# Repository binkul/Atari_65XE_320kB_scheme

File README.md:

# Atari_65XE_320kB_scheme

It is working, but there is problem with video. The image on the monitor is not clear. There is a lot of white vertical stripes - probably wrong GND project. 
There can be used up to four diffrent OS and eight internal languages, like MAC65, Action!, Basic XE, XL. On Board GTIA fixer and 256kB extra RAM.

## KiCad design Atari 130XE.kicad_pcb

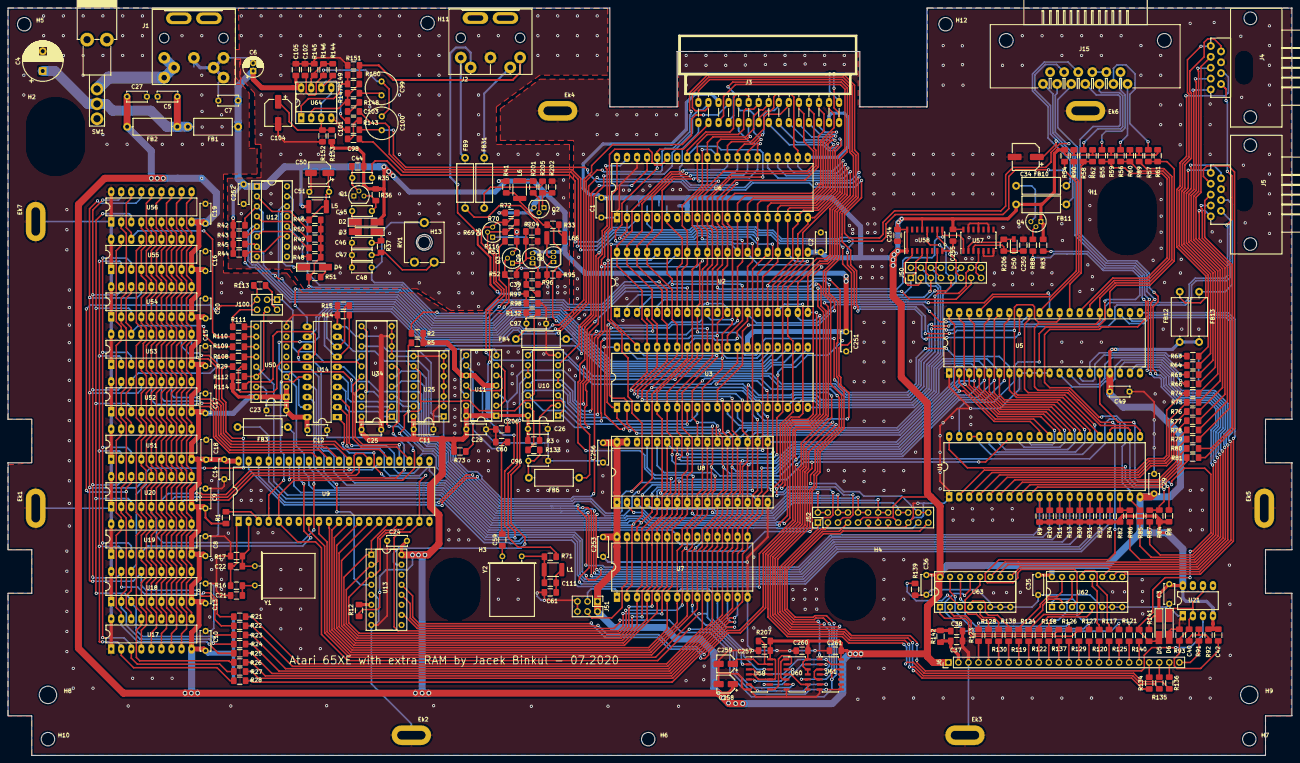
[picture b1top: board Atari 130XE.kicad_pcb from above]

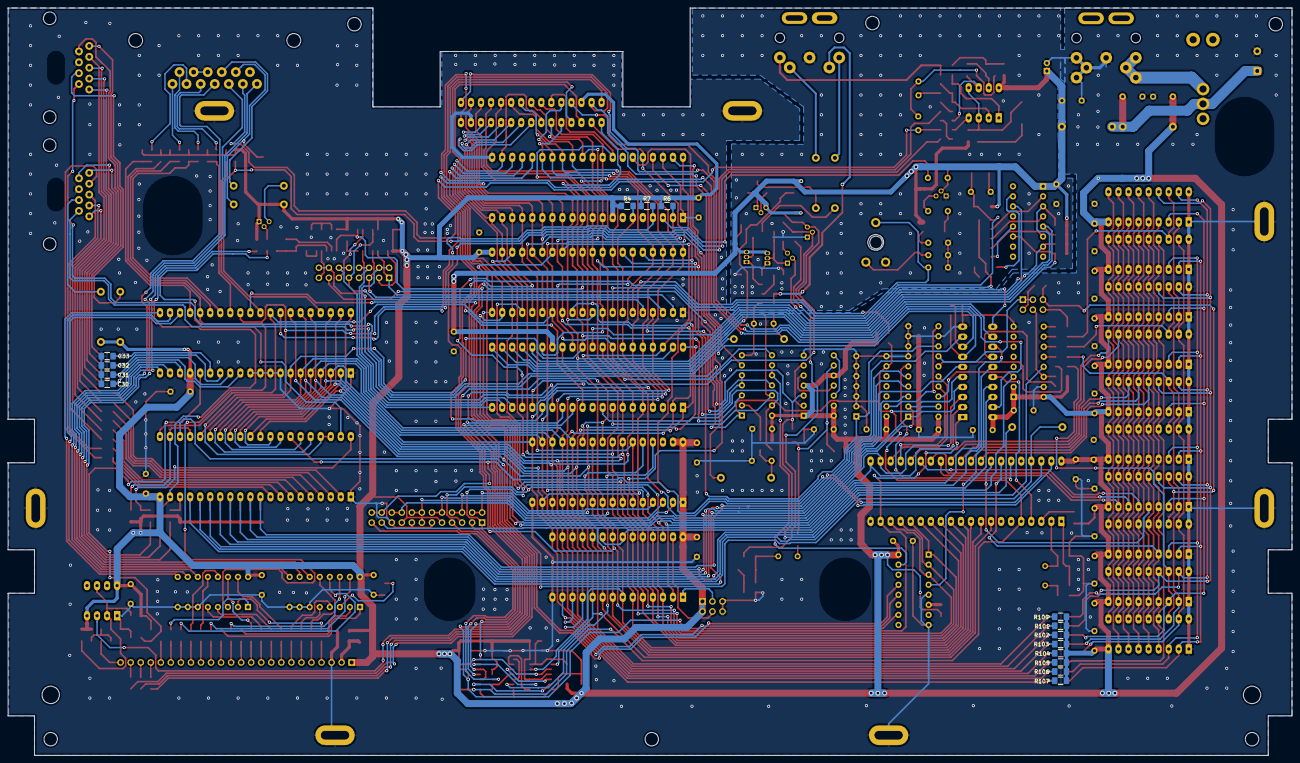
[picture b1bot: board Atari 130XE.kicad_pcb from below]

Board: 2 copper layers, 324.7 x 189.0 mm, 321 parts (15 on the bottom side), 305 nets.

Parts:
C1, C2, C3, C5, C7, C8, C15, C16, C17, C18, C19, C20, C23, C24, C25, C26, C27, C28, C29, C35, C36, C48, C49, C51, C251, C252, C253: 100nF; C_Disc_D5.0mm_W2.5mm_P5.00mm
C4: 470uF; CP_Radial_D10.0mm_P5.00mm
C6: 22uF; CP_Radial_D5.0mm_P2.00mm
C9, C10, C11, C12, C13, C14: C; C_Disc_D5.0mm_W2.5mm_P5.00mm
C21, C22: 27pF; C_1206_3216Metric_Pad1.42x1.75mm_HandSolder
C30, C31, C32, C33, C98, C103: 47nF; C_1206_3216Metric_Pad1.42x1.75mm_HandSolder
C34: 22uF; CP_Elec_6.3x5.3
C37: 10nF; C_1206_3216Metric_Pad1.42x1.75mm_HandSolder
C38, C61, C105, C254, C255, C257, C260, C261: 100nF; C_1206_3216Metric_Pad1.42x1.75mm_HandSolder
C39, C101, C102: 1nF; C_1206_3216Metric_Pad1.42x1.75mm_HandSolder
C40, C42: 100n; C_1206_3216Metric_Pad1.42x1.75mm_HandSolder
C44: 68pF; C_Disc_D5.0mm_W2.5mm_P5.00mm
C45: 220pF; C_Disc_D5.0mm_W2.5mm_P5.00mm
C46, C47, C96, C97: 1nF; C_Disc_D5.0mm_W2.5mm_P5.00mm
C50: 10uF; CP_Elec_5x5.7
C59, C206, C250: 22pF; C_1206_3216Metric_Pad1.42x1.75mm_HandSolder
C60: 560pF; C_1206_3216Metric_Pad1.42x1.75mm_HandSolder
C99, C100: 4,7uF; C_Radial_D8.0mm_H7.0mm_P3.50mm
C104: 10uF; CP_Elec_6.3x5.3
C111: 820pF; C_1206_3216Metric_Pad1.42x1.75mm_HandSolder
C256: 100nF; C_Disc_D6.0mm_W2.5mm_P5.00mm
C258: 22uF/16V; CP_Elec_4x5.3
C259: 4,7uF/35; CP_Elec_4x5.3
D2, D3, D4, D5: 1N4148; D_MiniMELF_Handsoldering
D6: 1N4001; D_MiniMELF_Handsoldering
D50: BAS316; D_SOD-323_HandSoldering
Ek1, Ek2, Ek3, Ek4, Ek5, Ek6, Ek7: Ekran_hole; Ekran_GND
FB1, FB2, FB3, FB4, FB5, FB9, FB10, FB11, FB12, FB13, FB31: Ferrite_Bead; L_Axial_L9.5mm_D4.0mm_P12.70mm_Horizontal_Fastron_SMCC
H1, H2: MountingHole; Big_hole
H3, H4: MountingHole; Medium_hole
H5, H6, H7, H10, H11, H12: MountingHole; Hole_3.4mm
H8, H9: MountingHole; Hole_4.4mm
H13: Pot hole; MountingHole_3.2mm_M3
J1: Power; DIN_7_pin
J2: DIN-5_180degree; DIN_5_pin
J3: Cartridge; Cartridge_Slot
J4, J5: Joystick_Port; Joystick_Pport
J6: Keyboard; PinHeader_1x24_P2.54mm_Vertical
J15: SIO_Port; SIO_Slot
J50: GTIA Fix; PinHeader_2x08_P2.54mm_Vertical
J51: OS Type; PinHeader_2x03_P2.54mm_Vertical
J52: Basic; PinHeader_2x12_P2.54mm_Vertical
J100: Ext_Memory_Conn; PinHeader_2x03_P2.54mm_Vertical
L1: 1,5uH; L_1812_4532Metric_Pad1.30x3.40mm_HandSolder
L5: 820uH; R_1812_4532Metric_Pad1.30x3.40mm_HandSolder
L6, L66: 100uH; L_1812_4532Metric_Pad1.30x3.40mm_HandSolder
Q1, Q2, Q3, Q6: 2N3904; TO-92
Q4: 2N3906; TO-92
Q8, Q9: PN2222A; TO-92_Inline
R1, R2, R3, R4, R5, R6, R7, R8, R9, R10, R11, R12, R13, R30, R31, R32, R34, R90, R114: 3k; R_1206_3216Metric_Pad1.42x1.75mm_HandSolder
R14, R15, R37, R41, R42, R43, R44, R45, R54, R72, R142, R146, R151, R206, R207: 1k; R_1206_3216Metric_Pad1.42x1.75mm_HandSolder
R16: 240; R_1206_3216Metric_Pad1.42x1.75mm_HandSolder
R17: 1M; R_1206_3216Metric_Pad1.42x1.75mm_HandSolder
R21, R22, R23, R24, R25, R26, R27, R28, R29, R96, R108, R109, R110, R111, R113: 33; R_1206_3216Metric_Pad1.42x1.75mm_HandSolder
R33: 5k6; R_1206_3216Metric_Pad1.42x1.75mm_HandSolder
R35: 33k; R_1206_3216Metric_Pad1.42x1.75mm_HandSolder
R36: 680; R_1206_3216Metric_Pad1.42x1.75mm_HandSolder
R46: 1k6; R_1206_3216Metric_Pad1.42x1.75mm_HandSolder
R47: 36k; R_1206_3216Metric_Pad1.42x1.75mm_HandSolder
R48: 18k; R_1206_3216Metric_Pad1.42x1.75mm_HandSolder
R49: 9k1; R_1206_3216Metric_Pad1.42x1.75mm_HandSolder
R50, R59, R60, R61, R62, R73, R82, R83, R84: 4k7; R_1206_3216Metric_Pad1.42x1.75mm_HandSolder
R51: 750; R_1206_3216Metric_Pad1.42x1.75mm_HandSolder
R52, R147: 2k; R_1206_3216Metric_Pad1.42x1.75mm_HandSolder
R53, R55, R56, R57, R58, R85, R86, R87, R91, R139: 100; R_1206_3216Metric_Pad1.42x1.75mm_HandSolder
R63, R64, R65, R66: 1k8; R_1206_3216Metric_Pad1.42x1.75mm_HandSolder
R69, R201: 6k8; R_1206_3216Metric_Pad1.42x1.75mm_HandSolder
R70, R100, R101, R102, R103, R104, R105, R106, R107, R112: 10k; R_1206_3216Metric_Pad1.42x1.75mm_HandSolder
R71, R134, R135, R136: 470; R_1206_3216Metric_Pad1.42x1.75mm_HandSolder
R74, R75, R76, R77, R78, R79, R80, R81: 120; R_1206_3216Metric_Pad1.42x1.75mm_HandSolder
R88: 2k7; R_1206_3216Metric_Pad1.42x1.75mm_HandSolder
R89, R141: 47k; R_1206_3216Metric_Pad1.42x1.75mm_HandSolder
R92, R143: 56k; R_1206_3216Metric_Pad1.42x1.75mm_HandSolder
R93, R148: 470k; R_1206_3216Metric_Pad1.42x1.75mm_HandSolder
R95, R202: 180; R_1206_3216Metric_Pad1.42x1.75mm_HandSolder
R97: 18; R_1206_3216Metric_Pad1.42x1.75mm_HandSolder
R98: 82; R_1206_3216Metric_Pad1.42x1.75mm_HandSolder
R116: 51; R_1206_3216Metric_Pad1.42x1.75mm_HandSolder
R117, R118, R119, R120, R121, R122, R123, R124, R125, R126, R127, R128, R129, R130, R132, R133, R137, R138: 220; R_1206_3216Metric_Pad1.42x1.75mm_HandSolder
R140: 270; R_1206_3216Metric_Pad1.42x1.75mm_HandSolder
R144, R152: 2k2; R_1206_3216Metric_Pad1.42x1.75mm_HandSolder
R145: 6k2; R_1206_3216Metric_Pad1.42x1.75mm_HandSolder
R149: 68k; R_1206_3216Metric_Pad1.42x1.75mm_HandSolder
R150: 5k1; R_1206_3216Metric_Pad1.42x1.75mm_HandSolder
R153: 3k3; R_1206_3216Metric_Pad1.42x1.75mm_HandSolder
R204: 47; R_1206_3216Metric_Pad1.42x1.75mm_HandSolder
R205: 150; R_1206_3216Metric_Pad1.42x1.75mm_HandSolder
RV1: R_POT; Potentiometer_ACP_CA9-V10_Vertical_Hole
SW1: Switch_power_on; Switch_ON-OFF
U1: PIA; DIP-40_W15.24mm_LongPads
U2: Antic; DIP-40_W15.24mm_LongPads
U3: GTIA; DIP-40_W15.24mm_LongPads
U5: POKEY; DIP-40_W15.24mm_LongPads
U6: Sally; DIP-40_W15.24mm_LongPads
U7: 27C512; DIP-28_W15.24mm_LongPads
U8: 27C010; DIP-32_W15.24mm_Socket_LongPads
U9: Freddie; DIP-40_W15.24mm_LongPads
U10: 74LS08; DIP-14_W7.62mm_Socket
U11: 74LS74; DIP-14_W7.62mm_Socket
U12: 4050; DIP-16_W7.62mm_Socket
U13: 74LS138; DIP-16_W7.62mm_Socket
U14: MMU; DIP-20_W7.62mm_LongPads
U17, U18, U19, U20, U51, U52, U53, U54, U55, U56: DRAM_4464; DIP-18_W7.62mm_LongPads
U21: NE555; DIP-8_W7.62mm_LongPads
U25: 74LS95; DIP-14_W7.62mm_Socket
U34: MMMU_GAL; DIP-20_W7.62mm_Socket
U50: 74LS155; DIP-16_W7.62mm_Socket
U57: 74HC14; SOIC-14_3.9x8.7mm_P1.27mm
U58: 74LS175; SOIC-16_3.9x9.9mm_P1.27mm
U59: 74HC74; SOIC-14_3.9x8.7mm_P1.27mm
U60, U61: 74HC02; SOIC-14_3.9x8.7mm_P1.27mm
U62, U63: 4051; DIP-16_W7.62mm_Socket
U64: LM358; DIP-8_W7.62mm_Socket_LongPads
Y1: 14,18757MHz; Crystal_HC18-U_Horizontal
Y2: 4.43MHz; Crystal_HC18-U_Horizontal

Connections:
+5VA: C6.1, C7.1, C105.2, C251.1, C252.1, D2.2, FB1.1, L5.1, Q2.3, Q8.3, Q9.3, R35.1, R36.1, R41.1, R42.1, R43.1, R44.1, R45.1, R72.2, R153.2, U3.27, U12.1, U64.8
A0: J3.5, U1.35, U2.13, U3.2, U5.36, U6.9, U7.10, U8.12, U9.8, U59.2
A1: J3.4, U1.36, U2.12, U3.1, U5.35, U6.10, U7.9, U8.11, U9.9
A2: J3.3, U2.11, U3.40, U5.34, U6.11, U7.8, U8.10, U9.10
A3: J3.2, U2.10, U3.39, U5.33, U6.12, U7.7, U8.9, U9.11, U59.12
A4: J3.C, U2.28, U3.38, U6.13, U7.6, U8.8, U9.12
A5: J3.D, U2.27, U6.14, U7.5, U8.7, U9.13
A6: J3.E, U2.26, U6.15, U7.4, U8.6, U9.14
A7: J3.F, U2.25, U6.16, U7.3, U8.5, U9.15
A8: J3.H, U2.24, U6.17, U7.25, U8.27, U9.16, U13.1
A9: J3.J, U2.23, U6.18, U7.24, U8.26, U9.17, U13.2
A10: J3.P, U2.16, U6.19, U7.21, U8.23, U9.18, U13.3
A11: J3.N, U2.22, U6.20, U7.23, U8.25, U9.19, U14.1
A12: J3.K, J52.1, U2.17, U6.22, U7.2, U9.21, U14.2, U61.3, U61.5
A12_cart: J52.3, U61.1
A12_sel: J52.2, J52.4, U8.4
A13: J52.5, U2.18, U6.23, U7.26, U9.22, U14.3
A13_cart: J52.7, U61.4
A13_sel: J52.6, J52.8, U8.28
A14: U2.19, U6.24, U14.4, U34.1
A14_sel: J52.10, J52.12, U8.29
A15: U2.20, U6.25, U14.5, U34.2
A15_sel: J52.14, J52.16, U8.3
A16_sel: J52.18, J52.20, U8.2
AN0: J50.1, U2.2, U58.4
AN0_FIX: J50.3, U58.2
AN1: J50.5, U2.3, U58.5
AN1_FIX: J50.7, U58.7
AN2: J50.9, U2.5, U58.12
AN2_FIX: J50.11, U58.10
AUDIO: J2.3, R150.1, R151.2
BACK0: J4.2, R75.1
BACK1: J5.2, R79.1
BASC_cart: J52.23, U60.10
BASIC: J52.21, U14.13, U60.6
BASIC_sel: J52.22, J52.24, U8.22, U8.24
BELL: C103.1, U3.15
BO2: J3.S, U1.25, U2.29, U3.30, U5.7, U10.3
BSC: J6.20, R140.1
CAS: U9.35, U34.6
CASBNK: J100.1, J100.3, U34.14
CASBNK_128: J100.5, R113.2, U19.16, U20.16
CASEXT_1: J100.6, R111.1
CASEXT_2: R108.1, U51.16, U52.16
CASEXT_3: R109.1, U53.16, U54.16
CASEXT_4: R110.1, U55.16, U56.16
CASINH: U9.4, U14.16
CASMAN: R29.2, U34.15
CCTL: J3.15, U13.10, U61.12
CHROMA: FB31.1, J2.5
CLKIN: J15.1, R56.1
CLKOUT: J15.2, R55.1
COMMAND: J15.7, R85.2
COMPOSITE: J2.4, R97.1, R98.1
D0: J3.10, R28.2, R107.2, U1.33, U2.30, U3.7, U5.38, U6.33, U7.11, U8.13
D1: J3.9, R27.2, R106.2, U1.32, U2.31, U3.6, U5.39, U6.32, U7.12, U8.14
D2: J3.8, R26.2, R105.2, U1.31, U2.32, U3.5, U5.40, U6.31, U7.13, U8.15
D3: J3.L, R25.2, R104.2, U1.30, U2.33, U3.4, U5.2, U6.30, U7.15, U8.17
D4: J3.6, R24.2, R103.2, U1.29, U2.40, U3.37, U5.3, U6.29, U7.16, U8.18
D5: J3.7, R23.2, R102.2, U1.28, U2.39, U3.36, U5.4, U6.28, U7.17, U8.19
D6: J3.11, R22.2, R101.2, U1.27, U2.38, U3.35, U5.5, U6.27, U7.18, U8.20
D7: J3.M, R21.2, R100.2, U1.26, U2.37, U3.34, U5.6, U6.26, U7.19, U8.21
DATAIN: J15.3, R57.1
DATAOUT: J15.5, R58.1
DQ0: R28.1, U17.2, U19.2, U51.2, U53.2, U55.2
DQ1: R27.1, U17.3, U19.3, U51.3, U53.3, U55.3
DQ2: R26.1, U17.15, U19.15, U51.15, U53.15, U55.15
DQ3: R25.1, U17.17, U19.17, U51.17, U53.17, U55.17
DQ4: R24.1, U18.2, U20.2, U52.2, U54.2, U56.2
DQ5: R23.1, U18.3, U20.3, U52.3, U54.3, U56.3
DQ6: R22.1, U18.15, U20.15, U52.15, U54.15, U56.15
DQ7: R21.1, U18.17, U20.17, U52.17, U54.17, U56.17
EXTSEL: R1.1, U9.3
FA14: U9.23, U34.16
FA15: U9.24, U34.17
FO0: U2.35, U3.29
FWD0: J4.1, R74.1
FWD1: J5.1, R78.1
GND: C1.2, C2.2, C3.2, C4.2, C5.2, C6.2, C7.2, C8.2, C9.2, C10.2, C11.2, C12.2, C13.2, C14.2, C15.2, C16.2, C17.2, C18.2, C19.2, C20.2, C21.2, C22.2, C23.2, C24.2, C25.2, C26.2, C27.2, C28.2, C29.2, C30.2, C31.2, C32.2, C33.2, C34.2, C35.2, C36.2, C37.2, C38.2, C46.1, C47.1, C48.1, C49.2, C50.2, C51.1, C60.2, C61.2, C96.2, C97.2, C101.1, C102.1, C104.2, C105.1, C206.2, C250.1, C251.2, C252.2, C253.2, C254.2, C255.2, C256.2, C257.2, C258.2, C259.2, C260.2, C261.2, D6.2, Ek1.1, Ek2.1, Ek3.1, Ek4.1, Ek5.1, Ek6.1, Ek7.1, J1.2, J1.3, J1.5, J1.7, J2.2, J3.B, J4.8, J5.8, J6.3, J15.4, J15.6, J51.5, J51.6, J52.11, J52.15, J52.19, Q1.1, Q6.1, R14.1, R15.1, R52.2, R53.2, R69.2, R93.2, R95.2, R98.2, R139.2, R145.1, R151.1, R152.1, R202.2, RV1.3, U1.1, U2.1, U3.3, U5.1, U5.8, U5.9, U5.10, U5.11, U6.1, U6.21, U6.38, U7.14, U8.16, U9.20, U10.7, U11.7, U12.8, U13.5, U13.8, U14.10, U17.1, U17.18, U18.1, U18.18, U19.1, U19.18, U20.1, U20.18, U21.1, U25.2, U25.3, U25.4, U25.5, U25.6, U25.7, U25.8, U34.7, U34.8, U34.9, U34.10, U34.12, U50.8, U50.15, U51.1, U51.18, U52.1, U52.18, U53.1, U53.18, U54.1, U54.18, U55.1, U55.18, U56.1, U56.18, U57.5, U57.7, U57.9, U57.11, U57.13, U58.8, U59.7, U60.7, U61.7, U62.6, U62.7, U62.8, U63.6, U63.7, U63.8, U64.4
GTIA: U3.32, U10.8
GTIA_AN0: J50.2, J50.4, U3.18
GTIA_AN1: J50.6, J50.8, U3.19
GTIA_AN2: J50.10, J50.12, U3.20
GTIA_NORM: C206.1, FB3.1, J50.13, U11.3
GTIA_OSC: J50.14, J50.16, U3.28
HALT: U2.9, U3.26, U6.35, U25.1, U34.13
IN0: J6.17, R117.1
IN1: J6.11, R118.1
IN2: J6.8, R119.1
IN3: J6.16, R120.1
IN4: J6.19, R121.1
IN5: J6.10, R122.1
IN6: J6.4, R123.1
IN7: J6.9, R124.1
INTERRUPT: J15.13, R86.2
IRQ: R7.2, U1.37, U1.38, U5.29, U6.4
K0: U5.23, U62.11
K1: U5.22, U62.10
K2: U5.21, U62.9
K3: U5.20, U63.11
K4: U5.19, U63.10
K5: U5.18, U63.9
KR1: R89.1, U5.25, U62.3
LEFT0: J4.3, R76.1
LEFT1: J5.3, R80.1
LHALT: U25.13, U34.11
LP: U2.4, U10.11
MONO: FB9.1, J2.1
MPD: R114.1, U14.14
MTRCTL: FB10.1, J15.8
NMI: R4.2, U2.7, U6.6
unnamed: C4.1, C5.1, FB1.2, FB2.1, SW1.2
unnamed: C21.1, R16.2, Y1.1
unnamed: C22.1, R17.2, U9.2, Y1.2
unnamed: C30.1, R66.2, U5.12
unnamed: C31.1, R65.2, U5.13
unnamed: C32.1, R64.2, U5.14
unnamed: C33.1, R63.2, U5.15
unnamed: C37.1, J6.2, R142.1
unnamed: C39.1, Q8.1, R95.1
unnamed: C39.2, R96.2, R97.2
unnamed: C40.1, C42.2, D6.1, R93.1, U21.2, U21.6
unnamed: C40.2, R91.1, R92.2
unnamed: C44.1, Q1.2, R35.2
unnamed: C45.1, D2.1, D3.2
unnamed: C45.2, Q1.3, R36.2
unnamed: C46.2, D3.1, R37.2
unnamed: C47.2, R37.1, RV1.1
unnamed: C48.2, RV1.2, U3.17
unnamed: C50.1, C51.2, L5.2, R46.1, R116.1
unnamed: C59.1, Y2.1
unnamed: C59.2, C60.1, R73.1, U11.9
unnamed: C96.1, FB5.2, R133.2
unnamed: C97.1, FB4.2, R132.2
unnamed: C98.1, R143.2
unnamed: C99.1, R147.2
unnamed: C99.2, C100.1, C102.2, R146.1
unnamed: C103.2, R148.2
unnamed: C104.1, R152.2, R153.1, U64.3, U64.5
unnamed: C111.1, L1.2, R71.1, Y2.2
unnamed: C61.1, C111.2, L1.1
unnamed: C250.2, D50.1, R206.2, U57.3
unnamed: C259.1, R207.2, U59.1, U59.13
unnamed: D4.1, U12.15
unnamed: D4.2, R51.2
unnamed: D5.2, R140.2, R141.2, U5.16
unnamed: D50.2, R206.1, U57.2
unnamed: FB9.2, R204.1
unnamed: FB10.2, Q4.3
unnamed: FB12.1, J4.7
unnamed: FB13.1, J5.7
unnamed: FB31.2, R205.1
unnamed: J1.1, J1.4, J1.6, SW1.3
unnamed: J51.3, U7.1
unnamed: J51.4, U7.27
unnamed: J100.2, R113.1
unnamed: J100.4, R112.1, U50.14
unnamed: L6.1, R33.2, R41.2, U3.21
unnamed: L6.2, R201.2
unnamed: L66.1, R33.1
unnamed: L66.2, Q8.2
unnamed: Q2.1, R202.1, R205.2
unnamed: Q2.2, R201.1
unnamed: Q3.1, Q9.2, R53.1, R204.2
unnamed: Q3.2, R46.2, R47.1, R48.1, R49.1, R50.1, R51.1, R52.1
unnamed: Q3.3, R116.2
unnamed: Q4.2, R88.2
unnamed: Q6.2, R69.1, R70.2, R71.2
unnamed: Q6.3, R70.1, R72.1, U3.16
unnamed: Q9.1, R96.1
unnamed: R3.1, U10.2
unnamed: R5.2, U2.6
unnamed: R8.2, U1.22, U1.24
unnamed: R12.1, U13.6
unnamed: R16.1, R17.1, U9.1
unnamed: R29.1, U17.16, U18.16
unnamed: R42.2, U3.24, U12.3
unnamed: R43.2, U3.23, U12.5
unnamed: R44.2, U3.22, U12.11
unnamed: R45.2, U3.31, U12.7
unnamed: R47.2, U12.6
unnamed: R48.2, U12.12
unnamed: R49.2, U12.4
unnamed: R50.2, U12.2
unnamed: R55.2, R59.2, U5.27
unnamed: R56.2, R60.2, U5.26
unnamed: R57.2, R61.2, U5.24
unnamed: R58.2, R62.2, U5.28
unnamed: R74.2, U1.2
unnamed: R75.2, U1.3
unnamed: R76.2, U1.4
unnamed: R77.2, U1.5
unnamed: R78.2, U1.6
unnamed: R79.2, U1.7
unnamed: R80.2, U1.8
unnamed: R81.2, U1.9
unnamed: R82.1, R86.1, U1.18
unnamed: R83.1, R85.1, U1.19
unnamed: R84.1, R87.1, U1.40
unnamed: R88.1, U1.39
unnamed: R90.1, U5.31
unnamed: R108.2, U50.12
unnamed: R109.2, U50.11
unnamed: R110.2, U50.10
unnamed: R111.2, U50.9
unnamed: R117.2, U62.13
unnamed: R118.2, U62.14
unnamed: R119.2, U62.15
unnamed: R120.2, U62.12
unnamed: R121.2, U62.1
unnamed: R122.2, U62.5
unnamed: R123.2, U62.2
unnamed: R124.2, U62.4
unnamed: R125.2, U63.13
unnamed: R126.2, U63.14
unnamed: R127.2, U63.15
unnamed: R128.2, U63.12
unnamed: R129.2, U63.1
unnamed: R130.2, U63.5
unnamed: R132.1, U3.8, U10.12
unnamed: R133.1, U3.9, U10.13
unnamed: R134.2, U3.12
unnamed: R135.2, U3.13
unnamed: R136.2, U3.14
unnamed: R137.2, U63.2
unnamed: R138.2, U63.4
unnamed: R139.1, U63.3
unnamed: R143.1, R144.2, U64.6
unnamed: R144.1, R145.2, R146.2, U64.7
unnamed: R147.1, R148.1, R149.2, U64.2
unnamed: R149.1, R150.2, U64.1
unnamed: U2.34, U10.4, U10.5
unnamed: U10.9, U10.10, U13.15
unnamed: U11.2, U11.6
unnamed: U11.5, U11.11
unnamed: U11.8, U11.12
unnamed: U3.25, U12.14
unnamed: U13.4, U14.17
unnamed: U59.5, U60.3
unnamed: U59.6, U61.6
unnamed: U59.8, U60.2
unnamed: U59.9, U61.2
unnamed: U59.3, U59.11, U61.13
unnamed: U60.1, U60.5
unnamed: U60.4, U60.8, U60.9
unnamed: U61.10, U61.11
O0: U6.37, U10.6
O1: C44.2, U6.3
O2: R2.1, U6.39, U9.5, U10.1, U25.9, U34.19, U61.8, U61.9
OPTION: J6.23, R136.1
OS: U7.20, U7.22, U14.15
OSC: FB3.2, U9.37, U57.1, U58.9
OSC_FIX: J50.15, U57.4
OUT0: J6.18, R125.1
OUT1: J6.13, R126.1
OUT2: J6.15, R127.1
OUT3: J6.5, R128.1
OUT4: J6.14, R129.1
OUT5: J6.6, R130.1
OUT6: J6.12, R137.1
OUT7: J6.7, R138.1
PB0: R9.2, U1.10, U14.9
PB1: R10.2, U1.11, U14.18
PB2: R11.2, U1.12, U34.3
PB3: R13.2, U1.13, U34.4
PB4: R30.2, U1.14, U34.5
PB5: R31.2, U1.15, U34.18, U50.3
PB6: R32.2, U1.16, U50.13
PB7: R34.2, U1.17, U14.6
PIA: U1.23, U13.12
POKEY: U5.30, U13.13
POTA01: J4.9, R64.1
POTA02: J5.9, R66.1
POTB01: J4.5, R63.1
POTB02: J5.5, R65.1
PROCEED: J15.9, R87.2
RA0: U9.32, U17.14, U18.14, U19.14, U20.14, U51.14, U52.14, U53.14, U54.14, U55.14, U56.14
RA1: U9.31, U17.13, U18.13, U19.13, U20.13, U51.13, U52.13, U53.13, U54.13, U55.13, U56.13
RA2: U9.30, U17.12, U18.12, U19.12, U20.12, U51.12, U52.12, U53.12, U54.12, U55.12, U56.12
RA3: U9.29, U17.11, U18.11, U19.11, U20.11, U51.11, U52.11, U53.11, U54.11, U55.11, U56.11
RA4: U9.28, U17.8, U18.8, U19.8, U20.8, U51.8, U52.8, U53.8, U54.8, U55.8, U56.8
RA5: U9.27, U17.7, U18.7, U19.7, U20.7, U51.7, U52.7, U53.7, U54.7, U55.7, U56.7
RA6: U9.26, U17.6, U18.6, U19.6, U20.6, U51.6, U52.6, U53.6, U54.6, U55.6, U56.6
RA7: U9.25, U17.10, U18.10, U19.10, U20.10, U51.10, U52.10, U53.10, U54.10, U55.10, U56.10
RAS: U9.33, U17.5, U18.5, U19.5, U20.5, U51.5, U52.5, U53.5, U54.5, U55.5, U56.5
RD4: J3.A, R14.2, U14.7
RD5: J3.14, R15.2, U3.11, U14.8
RDY: R6.2, U2.15, U6.2
READY: C34.1, FB11.1, J15.10
REF: U2.8, U14.11
RESET: J6.24, R91.2
RIGHT0: J4.4, R77.1
RIGHT1: J5.4, R81.1
RST: U1.34, U2.36, U6.40, U9.39, U21.3
R\W: J3.R, U1.21, U2.14, U3.33, U5.32, U6.36, U9.38
S4: J3.1, U14.19
S5: J3.12, U14.12
SELECT: J6.22, R135.1
SIOAUDIO: C100.2, C101.2, J15.11
SOUND: C98.2, R54.2, U5.37
START: J6.21, R134.1
TRIG0: FB4.1, J4.6
TRIG1: FB5.1, J5.6
VCC: C1.1, C2.1, C3.1, C8.1, C9.1, C10.1, C11.1, C12.1, C13.1, C14.1, C15.1, C16.1, C17.1, C18.1, C19.1, C20.1, C23.1, C24.1, C25.1, C26.1, C27.1, C28.1, C29.1, C35.1, C36.1, C38.1, C42.1, C49.1, C253.1, C254.1, C255.1, C256.1, C257.1, C258.1, C260.1, C261.1, D5.1, FB2.2, FB11.2, FB12.2, FB13.2, J3.13, J6.1, J51.1, J51.2, J52.9, J52.13, J52.17, Q4.1, R1.2, R2.2, R3.2, R4.1, R5.1, R6.1, R7.1, R8.1, R9.1, R10.1, R11.1, R12.2, R13.1, R30.1, R31.1, R32.1, R34.1, R54.1, R59.1, R60.1, R61.1, R62.1, R73.2, R82.2, R83.2, R84.2, R89.2, R90.2, R92.1, R100.1, R101.1, R102.1, R103.1, R104.1, R105.1, R106.1, R107.1, R112.2, R114.2, R141.1, R142.2, R207.1, U1.20, U2.21, U5.17, U6.8, U7.28, U8.1, U8.31, U8.32, U9.40, U10.14, U11.1, U11.4, U11.10, U11.13, U11.14, U13.16, U14.20, U17.9, U18.9, U19.9, U20.9, U21.4, U21.8, U25.14, U34.20, U50.1, U50.2, U50.16, U51.9, U52.9, U53.9, U54.9, U55.9, U56.9, U57.14, U58.1, U58.13, U58.16, U59.4, U59.10, U59.14, U60.11, U60.12, U60.14, U61.14, U62.16, U63.16
WRT: U9.34, U17.4, U18.4, U19.4, U20.4, U51.4, U52.4, U53.4, U54.4, U55.4, U56.4

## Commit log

2020-10-25 Complete scheme
